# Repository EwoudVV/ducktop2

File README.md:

# Ducktop2

current case model, 10 october 2026. the lid and base share a 370 x 274 mm
outline, and the radio is planned as an external accessory. i'm aiming for
33.3 mm closed without feet. the right-side cooler and power guides now
clear the saved geometry, with no board cutout. the fan and fins now have
separate supports, with a bottom intake grille and a duct to the side.
the five selected feet bring the nominal total to 37.4 mm. the fan lead
extension has a route and removable clamp; the loaded intake gap and
finished wiring still need a physical check.
the cpu clamp and real material, load and cooling tests are still needed.
[case CAD and fit notes](mechanical/flush-case/README.md)

i'm building a 16-inch x86 laptop around the LattePanda Mu Ultra. i wanted the
exposed hardware and flexibility of a cyberdeck in something i could
actually carry around and use every day.

ducktop1 used a Pi 500+ and a portable monitor, with HDMI and USB-C cables
looping around the outside of the case. ducktop2 brings the display onto
direct eDP and puts power, ports, and laptop controls on custom boards.

## what's in it

- LattePanda Mu Ultra 226V initially, with the carrier designed to support a later 256V upgrade; 16 GB RAM and NVMe storage
- 16-inch AUO B160QAN03.K, targeting 2560x1600 at 120 Hz over direct eDP
- M.2 NVMe and a separate Wi-Fi/Bluetooth socket
- 65-key Cherry MX Ultra Low Profile keyboard and a 140 x 105 mm USB trackpad
- five USB-C ports, two USB-A ports, HDMI, and Gigabit Ethernet
- a 3S battery, USB-C PD charging from either side, and AUX/DC input
- STM32F407 for laptop control and a separate RP2350 with protected maker GPIO
- two status OLEDs, speakers, a headphone jack, and a microphone
- optional external VHF/UHF radio and GNSS accessory, with its own audio path

## build status

updated 16 october 2026. the carrier interface is being switched to Mu
Ultra: 226V first, with a later 256V upgrade. the new pin map moves HDMI to
TCP2, reallocates USB and gives NVMe a real clock-request connection. the
100 W power circuit is saved, but placement, routing, cooling and hardware
qualification still need work. the
[module requirements](manufacturing/lattepanda_mu_bios_release.md) separate
that target from the current CAD and the remaining hardware checks.

the revised power circuits, separate power wiring and signal connectors are
saved on all three main boards. the new placement pass uses both sides:
local capacitors sit near their actual supply pins, USB protection follows
its connector, and the audio and maker circuits have been regrouped.
the connector positions, mounting points and board gaps are preserved.
the existing PCIe routing is intact. the latest pass moves 31 power parts,
adds five local capacitors, repairs the right USB-C control routes and
corrects three USB protection footprints to their proper 0.4 mm pitch.
[placement and checks](docs/hardware/mainboard-power-placement.md) cover
those changes.

20 october: the charger and the Mu supply are routed, including both
controllers and a VSYS island on In4. their local parts were re-placed so the
fine-pitch controller pins could escape cleanly.
[charger and Mu supply routing](docs/hardware/charger-and-mu-routing.md)
has the details. the input selectors, battery path, fuel gauge and
always-on chain are routed locally as well; both selectors moved to the back
and the gauge shunt now sits beside the battery terminal.
[input and battery routing](docs/hardware/input-and-battery-routing.md)
covers that pass. DRC has no new findings and the unconnected count dropped
from 1,798 to 1,308. the long feeds from the side terminals and most of the
main-board routing still remain.

the keyboard has per-key RGB on four layers and its routing is complete.
the RGB buffer has separate 3.3 V and 5 V supplies. the key positions,
outline and cable connector are unchanged. [keyboard routing notes](keyboard/README.md)
cover the LEDs, current limit and switch keepouts. the old non-RGB order
files have been retired. the radio antenna connectors now match the board edge and their
mechanical drawing. the radio still needs routing.

the four-layer BMS is routed for stronger battery operation, with
an 8 A discharge target and up to 3 A charging. it now uses a BQ76922,
independent current guards and a limited startup branch. the 80 mm board
has zero unconnected items and zero physical DRC findings, including the
stricter fabrication checks. its first assembly leaves the three drive links
out for programming and bench tests. the matching center-board cutout is
saved. [power and battery](docs/hardware/power-and-battery.md) describes the
circuit and the measurements needed before using it with the cells.
the three main-board sections are eight layers,
and most of their routing still remains. [power revision status](docs/hardware/power-revision.md)
records what is saved and what is still unfinished.

firmware corrections cover charger communication, startup, watchdog and fan
handling, USB power permissions, and host communication. assembled-hardware
tests are still pending. the replacement panel has run at 2560x1600 and
120 Hz on the Intehill controller; the final Mu-to-panel cable still needs
validation. the complete laptop is not ready for fabrication or powered
integration.

## boards

```mermaid
flowchart LR
    L[Left I/O] <-->|signal cable and power wiring| C[Center: Mu, EC, charger, gauge, maker MCU]
    C <-->|signal cable and power wiring| R[Right I/O]
    B[BMS: cell monitoring and protection] <-->|power and isolated control wiring| C
    Cells[3S cells and cell taps] --- B
    C --- K[Keyboard]
    C --- Radio[Optional external radio and GNSS]
    C -->|Mu onboard eDP| Panel[Internal display]
```

the center charges the whole pack. the BMS monitors the cell taps and
controls the protection FETs. balancing is disabled in the prototype profile.
the EC and maker controller have separate jobs,
and the rest of the laptop is intended to work with the radio board removed.

## open in KiCad

the current reference version is KiCad 10.0.4.

| Work | File |
| --- | --- |
| Center schematic | `ducktop2.kicad_pro` |
| Center layout | `ducktop2-center.kicad_pcb` |
| Left I/O | `left_io/left_io.kicad_pro` |
| Right I/O | `right_io/right_io.kicad_pro` |
| BMS | `bms/bms.kicad_pro` |
| Keyboard | `keyboard/12_keyboard_daughterboard.kicad_pro` |
| Radio | `radio_daughterboard/radio_daughterboard.kicad_pro` |

read [build and verification](docs/build-and-verify.md) before regenerating
or syncing a board. the center schematic and PCB have different basenames.
review an explicit current netlist before updating the PCB; rebuilding a
board can replace existing routing.

## files and documentation

| Location | Contents |
| --- | --- |
| Root KiCad files | Center project and active schematic hierarchy |
| `left_io/`, `right_io/`, `bms/`, `keyboard/`, `radio_daughterboard/` | Separate board projects |
| `gen/` | Schematic generators, validation code, and symbol definitions |
| `ducktop2.pretty/`, `Module_LattePanda.pretty/`, `ducktop2.3dshapes/` | Shared footprints and models |
| `docs/hardware/` | Circuit, cable, display, and mechanical documentation |
| `firmware/` | EC/maker code, tests, and firmware release records |
| `mechanical/` | Floorplan, case CAD, layout planner and fit checks |
| `reference/` | Source/reference designs and retained generator inputs |
| `manufacturing/` | Board packages, quotes, and manufacturing requirements |
| `verification/` | Hardware validation record and ignored generated checks |
| `software/` | Fedora setup, recovery, and theme files |

- [hardware and behavior](docs/hardware/overview.md)
- [power and battery](docs/hardware/power-and-battery.md)
- [cables and connectors](docs/hardware/cables-and-connectors.md)
- [display harness](docs/hardware/display-direct-edp.md)
- [mechanical layout](docs/hardware/mechanical.md)
- [build and verify](docs/build-and-verify.md)
- [bring-up procedure](docs/BRINGUP_TEST_PLAN.md)
- [parts and cost](docs/bom-and-cost.md)
- [firmware](firmware/README.md)
- [manufacturing](manufacturing/README.md)
- [OS work](software/os-theme/README.md)
- [ducktop1](docs/ducktop1.md)
- [Forge project pitch](docs/forgery_pitch.md)
- [project journal](JOURNAL.md)

## sponsors

thanks to NextPCB for supporting PCB manufacturing and assembly for ducktop2!

## license

the project files are under the [MIT license](LICENSE).

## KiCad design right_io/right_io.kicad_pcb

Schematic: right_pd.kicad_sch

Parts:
C1760: 100n branch input; C_0603_1608Metric; MPN GRM188R71H104KA93D
C1761: 100n TPS25810 IN HF; C_0603_1608Metric; MPN GRM188R71H104KA93D
C1762: 150u 10V TPS25810 input reservoir; CP_EIA-7343-31_Kemet-D; MPN T520D157M010ATE025
C1763: 10u protected VBUS_SYS; C_1206_3216Metric; MPN GRM31CR71A106KA01L
C1764: 100n TPS25810 AUX; C_0603_1608Metric; MPN GRM188R71H104KA93D
C1770: 1u 50V connector-side VBUS; C_0805_2012Metric; MPN GRM21BR71H105KA12L
C1771: 1u TPD1S514 VBUS_POWER stability; C_0603_1608Metric; MPN GRM188R71A105KA61D
C2040: 100n 100V TPD4S201 VBIAS; C_0805_2012Metric; MPN GRM21BR72A104KA01L
C2041: 820n 10V TPD4S201 VPWR; C_0805_2012Metric; MPN GRM21BR71A824KA01L
C2042: 100n EEPROM local; C_0603_1608Metric; MPN GRM188R71H104KA93D
C2043: 100n mux-control buffer local; C_0603_1608Metric; MPN GRM188R71H104KA93D
C2055: 4.7u 25V raw VBUS; pre-attach total below 10uF; C_1206_3216Metric; MPN GRM31CR71E475KA88L
C2056, C2057, C2058, C2059: 10n 50V connector VBUS HF; C_0402_1005Metric; MPN GRM155R71H103KA88D
C2060: 10u 25V X7R; C_1206_3216Metric; MPN GRM31CR71E106KA12L
C2061, C2693: 4.7u 25V X7R; C_1206_3216Metric; MPN GRM31CR71E475KA88L
C2062: 10u 10V X7R; C_1206_3216Metric; MPN GRM31CR71A106KA01L
C2063, C2064: 270p C0G; C_0402_1005Metric; MPN GRM1555C1H271JA01D
C2065, C2066: 100u 10V PP5V source bulk; CP_EIA-7343-31_Kemet-D; MPN T520D107M010ATE070
C2067: 10u PP5V local ceramic; C_1206_3216Metric; MPN GRM31CR71A106KA01L
C2068: 68u 25V PPHV sink bulk; CP_EIA-7343-31_Kemet-D; MPN T521V686M025ATE050
C2069: 100n 50V PPHV local; C_0603_1608Metric; MPN GRM188R71H104KA93D
C2070: 100n USB2 switch local; C_0603_1608Metric; MPN GRM188R71H104KA93D
C2090: 100n 50V input local; C_0603_1608Metric; MPN GRM188R71H104KA93D
C2091: 10u 25V output; C_1206_3216Metric; MPN GRM31CR71E106KA12L
C2092: 10n 50V C0G slew control; C_0603_1608Metric; MPN GRM1885C1H103JA01D
C2404: 1u; C_0805_2012Metric; MPN GRM21BR71H105KA12L
C2409: 100n; C_0603_1608Metric; MPN GRM188R71H104KA93D
C2414: 4.7n C0G PP5V slew; C_0603_1608Metric; MPN GRM1885C1H472JA01D
C2631: 100n 50V inverter bypass; C_0603_1608Metric; MPN GRM188R71H104KA93D
C2681: 100n 50V qualifier bypass; C_0603_1608Metric; MPN GRM188R71H104KA93D
D2090: B340A eFuse output negative-transient clamp; D_SMA; MPN B340A-13-F
H13, H15, H17: M2.5 isolated mainboard mounting hole; MountingHole_2.7mm_M2.5
J11: USB-C dual-role data/PD port J11; USB_C_Receptacle_Molex_105450-0101; MPN 105450-0101
J12: USB-C source-only data port J12; USB_C_Receptacle_Molex_105450-0101; MPN 105450-0101
Q2002: 2N7002K DFP USB2 enable inverter; SOT-23; MPN 2N7002KT1G
Q2631: BSS138 switched discharge; SOT-23; MPN BSS138LT1G
R1760: 19.1k 1% TPS2553 VBUS plus VCONN ILIM; R_0603_1608Metric; MPN RC0603FR-0719K1L
R1761: 4.99k POL pull-up; R_0603_1608Metric; MPN RC0603FR-074K99L
R1762: 100k 1% TPS25810 REF; R_0603_1608Metric; MPN RC0603FR-07100KL
R1770: 249R 0.25W TPS25810 OUT discharge; R_1206_3216Metric; MPN RC1206FR-07249RL
R2040: 10k shared CC/USB2 protector FLT pull-up; R_0603_1608Metric; MPN RC0603FR-0710KL
R2041: 2.2k EEPROM SDA pull-up; R_0603_1608Metric; MPN RC0603FR-072K2L
R2042: 2.2k EEPROM SCL pull-up; R_0603_1608Metric; MPN RC0603FR-072K2L
R2043: 4.7k TCPC SDA pull-up; R_0603_1608Metric; MPN RC0603FR-074K7L
R2044: 4.7k TCPC SCL pull-up; R_0603_1608Metric; MPN RC0603FR-074K7L
R2045: 10k TCPC IRQ pull-up; R_0603_1608Metric; MPN RC0603FR-0710KL
R2046: 10k mux FLIP pull-up; R_0603_1608Metric; MPN RC0603FR-0710KL
R2047: 10k mux EN pull-up; R_0603_1608Metric; MPN RC0603FR-0710KL
R2055: 10k I2Cc IRQ inactive pull-up; R_0603_1608Metric; MPN RC0603FR-0710KL
R2056: 100k USB2 switch default-disable pull-up; R_0603_1608Metric; MPN RC0603FR-07100KL
R2057: 0R protector FLT wired-OR link; R_0603_1608Metric; MPN RC0603FR-070RL
R2090: 1k 1W switched input discharge; R_2512_6332Metric; MPN RC2512FR-071KL
R2091: 100k discharge gate default-low; R_0603_1608Metric; MPN RC0603FR-07100KL
R2092: 1k IMON load; R_0603_1608Metric; MPN RC0603FR-071KL
R2093: 267R 0.1% sink breaker; 5.58A nominal; R_0603_1608Metric; MPN RT0603BRD07267RL
R2094: 47k sink enable default-off; R_0603_1608Metric; MPN RC0603FR-0747KL
R2095: 10k sink enable series; R_0603_1608Metric; MPN RC0603FR-0710KL
R2096: 150k sink PG pull-up; valid with input off; R_0603_1608Metric; MPN RC0603FR-07150KL
R2404, R2409: 100k; R_0603_1608Metric; MPN RC0603FR-07100KL
R2414: 10k; R_0603_1608Metric; MPN RC0603FR-0710KL
U42: TPS25751AD USB-PD DRP controller; Texas_REF0038A_WQFN-38-2EP_6x4mm_P0.4; MPN TPS25751ADREFR
U721: TPS259827ONRGER PD2 sink breaker; Texas_RGE0024M_QFN24_4x4_2EP; MPN TPS259827ONRGER
U1760: TPS2553DDBVR 1.3A USB branch; SOT-23-6; MPN TPS2553DDBVR
U1761: TPS25810RVCR Type-C DFP controller; Texas_RVC0020A_WQFN-20-1EP_3x4mm_P0.5mm_EP1.6x2.6mm; MPN TPS25810RVCR
U1763: TPD1S514-1YZR 5.9V VBUS OVP; Texas_TPD1S514_YZ0012_1.99x1.29mm_P0.4mm; MPN TPD1S514-1YZR
U1765: TPD4E05U06 USB2/CC ESD; USON-10_2.5x1.0mm_P0.5mm; MPN TPD4E05U06DQAR
U2011: TPD4S201 CC and USB2 short-to-VBUS protector; Texas_RUK0020B_WQFN-20-1EP_3x3mm_P0.4mm_EP1.7x1.7mm_Thermal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; MPN TPD4S201RUKR
U2012: CAT24C256 32KB private TPS25751A EEPROM; SOIC-8_3.9x4.9mm_P1.27mm; MPN CAT24C256WI-GT3
U2013: TS3USB30E DFP-qualified USB2 disconnect; TSSOP-10_3x3mm_P0.5mm; MPN TS3USB30EDGSR
U2014: SN74LVC2G07 partial-power-down mux controls; SOT-363_SC-70-6; MPN SN74LVC2G07DCKR
U2015: TVS2200 22V USB VBUS surge clamp; WSON-6-1EP_2x2mm_P0.65mm_EP1x1.6mm; MPN TVS2200DRVR
U2016: SN74LVC1G08 DFP and attached qualifier; SOT-23-5; MPN SN74LVC1G08DBVR
U2404: TPS22992SRXNR J11 PP5V gate; Texas_RXN0008A_WQFN-HR-8_1.25x1.25mm; MPN TPS22992SRXNR
U2409: SN74LVC1G08DBVR J12 source permission; SOT-23-5; MPN SN74LVC1G08DBVR
U2631: SN74LVC1G04DBVR discharge control; SOT-23-5; MPN SN74LVC1G04DBVR

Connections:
/HUB_DS1_DN: U2013.8 (D1-); also elsewhere on the board
/HUB_DS1_DP: U2013.2 (D1+); also elsewhere on the board
/HUB_DS4_DN: J12.A7 (D-), J12.B7 (D-), U1765.2 (D1-); also elsewhere on the board
/HUB_DS4_DP: J12.A6 (D+), J12.B6 (D+), U1765.1 (D1+); also elsewhere on the board
/HUB_PRT_CTL4: U1760.4 (~FAULT), U1761.1 (~FAULT), U2409.2; also elsewhere on the board
/MCU_3V3: C2062.1, C2409.1, C2631.1, R2040.1, R2043.1, R2044.1, R2045.1, R2096.1, U42.38 (VIN_3V3), U2409.5 (VCC), U2631.5 (VCC); also elsewhere on the board
/PD2 Dual-Role/J11_PP5V_CT: C2414.1, U2404.7 (CT)
/PD2 Dual-Role/J12_5V_PRE: C1761.1, C1762.1, U1760.6 (OUT), U1761.2 (IN1), U1761.3 (IN1), U1761.4 (IN2)
/PD2 Dual-Role/J12_CC1: J12.A5 (CC1), U1761.11 (CC1), U1765.4 (D2+)
/PD2 Dual-Role/J12_CC2: J12.B5 (CC2), U1761.13 (CC2), U1765.5 (D2-)
/PD2 Dual-Role/J12_ILIM: R1760.1, U1760.5 (ILIM)
/PD2 Dual-Role/J12_POL_N: R1761.2, U1761.18 (~POL)
/PD2 Dual-Role/J12_REF: R1762.1, U1761.10 (REF)
/PD2 Dual-Role/J12_REF_RTN: R1762.2, U1761.9 (REF_RTN)
/PD2 Dual-Role/J12_VBUS: C1770.1, J12.A4 (VBUS), J12.A9 (VBUS), J12.B4 (VBUS), J12.B9 (VBUS), U1763.B3 (VBUS_CON), U1763.C2 (VBUS_CON), U1763.C3 (VBUS_CON)
/PD2 Dual-Role/J12_VBUS_POWER: C1771.1, U1763.B1 (VBUS_POWER)
/PD2 Dual-Role/J12_VBUS_SYS: C1763.1, R1770.1, U1761.14 (OUT), U1761.15 (OUT), U1763.A2 (VBUS_SYS), U1763.A3 (VBUS_SYS), U1763.B2 (VBUS_SYS)
/PD2 Dual-Role/PD2_CC1_CONN: J11.A5 (CC1), U2011.4 (C_CC1), U2011.7 (RPD_G1)
/PD2 Dual-Role/PD2_CC1_SYS: C2063.1, U42.28 (CC1), U2011.12 (CC1)
/PD2 Dual-Role/PD2_CC2_CONN: J11.B5 (CC2), U2011.5 (C_CC2), U2011.6 (RPD_G2)
/PD2 Dual-Role/PD2_CC2_SYS: C2064.1, U42.29 (CC2), U2011.11 (CC2)
/PD2 Dual-Role/PD2_CC_ESD_VBIAS: C2040.1, U2011.3 (VBIAS)
/PD2 Dual-Role/PD2_CC_FAULT_LOCAL_N: R2057.1, U2011.9 (FLT)
/PD2 Dual-Role/PD2_CONN_DN: J11.A7 (D-), J11.B7 (D-), U2011.2 (C_SBU2)
/PD2 Dual-Role/PD2_CONN_DP: J11.A6 (D+), J11.B6 (D+), U2011.1 (C_SBU1)
/PD2 Dual-Role/PD2_DISCHARGE: Q2631.1 (G), R2091.1, U2631.4
/PD2 Dual-Role/PD2_DISCHARGE_DRAIN: Q2631.3 (D), R2090.2
/PD2 Dual-Role/PD2_DRAIN_THERMAL: U42.15 (DRAIN), U42.30 (DRAIN), U42.40 (DRAIN)
/PD2 Dual-Role/PD2_EEPROM_IRQ_N: R2055.2, U42.18 (I2Cc_IRQ)
/PD2 Dual-Role/PD2_EEPROM_SCL: R2042.2, U42.17 (I2Cc_SCL), U2012.6 (SCL)
/PD2 Dual-Role/PD2_EEPROM_SDA: R2041.2, U42.16 (I2Cc_SDA), U2012.5 (SDA)
/PD2 Dual-Role/PD2_EFUSE_DVDT: C2092.1, U721.15 (dVdt)
/PD2 Dual-Role/PD2_EFUSE_ILIM: R2093.1, U721.8 (ILIM)
/PD2 Dual-Role/PD2_EFUSE_IMON: R2092.1, U721.9 (IMON)
/PD2 Dual-Role/PD2_EFUSE_SHDN: R2094.1, R2095.2, U721.6 (EN/UVLO)
/PD2 Dual-Role/PD2_GPIO_ATTACH: U42.36 (GPIO7), U2016.2
/PD2 Dual-Role/PD2_GPIO_DFP: U42.26 (GPIO4/USB_P), U2016.1
/PD2 Dual-Role/PD2_GPIO_FLIP: U42.37 (GPIO6), U2014.1
/PD2 Dual-Role/PD2_HOST_ATTACHED: U2014.3, U2016.4
/PD2 Dual-Role/PD2_HOST_SWITCHED_DN: U2011.14 (SBU2), U2013.6 (D-)
/PD2 Dual-Role/PD2_HOST_SWITCHED_DP: U2011.15 (SBU1), U2013.4 (D+)
/PD2 Dual-Role/PD2_LDO1V5: C2061.1, C2693.1, U42.4 (LDO_1V5)
/PD2 Dual-Role/PD2_LDO3V3: C2041.1, C2042.1, C2060.1, R2041.1, R2042.1, R2055.1, U42.1 (LDO_3V3), U2011.10 (VPWR), U2012.8 (VCC)
/PD2 Dual-Role/PD2_MUX_EN: Q2002.1 (G), R2047.2, U2014.4
/PD2 Dual-Role/PD2_MUX_FLIP: R2046.2, U2014.6
/PD2 Dual-Role/PD2_PP5V_GATED: C2065.1, C2066.1, C2067.1, R2414.1, U42.34 (PP5V_(34-35)), U2404.5 (QOD), U2404.6 (VOUT)
/PD2 Dual-Role/PD2_PPHV: C2068.1, C2069.1, C2090.1, U42.20 (PPHV_(20-22)), U721.1 (IN), U721.2 (IN), U721.3 (IN), U721.16 (IN), U721.25 (IN)
/PD2 Dual-Role/PD2_USB2_OE_N: Q2002.3 (D), R2056.2, U2013.9 (~OE)
/PD2 Dual-Role/USB_J12_SWITCH_EN: U1760.3 (EN), U1761.6 (EN), U2409.4
/PD2_EFUSE_PG: R2096.2, U721.13 (PG); also elsewhere on the board
/PD2_I2C_SCL: R2044.2, U42.9 (I2Ct_SCL); also elsewhere on the board
/PD2_I2C_SDA: R2043.2, U42.8 (I2Ct_SDA); also elsewhere on the board
/PD2_PATH_EN: R2095.1, U2631.2; also elsewhere on the board
/PD2_SOURCE_PG: R2414.2, U2404.3 (PG); also elsewhere on the board
/PD2_TCPC_IRQ_N: R2045.2, U42.10 (I2Ct_IRQ); also elsewhere on the board
/PD2_VBUS_GATED: C2091.1, D2090.1 (K), R2090.1, U721.17 (OUT), U721.18 (OUT), U721.19 (OUT), U721.20 (OUT), U721.21 (OUT), U721.22 (OUT), U721.23 (OUT), U721.24 (OUT); also elsewhere on the board
/PD2_VBUS_RAW: C2055.1, C2056.1, C2057.1, C2058.1, C2059.1, J11.A4 (VBUS), J11.A9 (VBUS), J11.B4 (VBUS), J11.B9 (VBUS), U42.23 (VBUS_IN_(23-25)), U42.32 (VBUS_(32-33)), U2015.4 (IN), U2015.5 (IN), U2015.6 (IN); also elsewhere on the board
/PD_PROTECT_FAULT_N: R2040.2, R2057.2; also elsewhere on the board
/SYS_3V3: C1764.1, C2043.1, C2070.1, C2681.1, R1761.1, R2046.1, R2047.1, R2056.1, U1761.5 (AUX), U2013.10 (VCC), U2014.5 (VCC), U2016.5 (VCC); also elsewhere on the board
/USB_J11_PERMIT: R2404.1, U2404.8 (ON); also elsewhere on the board
/USB_J12_PERMIT: R2409.1, U2409.1; also elsewhere on the board
/USB_PORT_5V: C1760.1, C2404.1, U1760.1 (IN), U2404.1 (VBIAS), U2404.2 (VIN); also elsewhere on the board
GND: C1760.2, C1761.2, C1762.2, C1763.2, C1764.2, C1770.2, C1771.2, C2040.2, C2041.2, C2042.2, C2043.2, C2055.2, C2056.2, C2057.2, C2058.2, C2059.2, C2060.2, C2061.2, C2062.2, C2063.2, C2064.2, C2065.2, C2066.2, C2067.2, C2068.2, C2069.2, C2070.2, C2090.2, C2091.2, C2092.2, C2404.2, C2409.2, C2414.2, C2631.2, C2681.2, C2693.2, D2090.2 (A), J11.A1 (GND), J11.A12 (GND), J11.B1 (GND), J11.B12 (GND), J11.SH (SHIELD), J12.A1 (GND), J12.A12 (GND), J12.B1 (GND), J12.B12 (GND), J12.SH (SHIELD), Q2002.2 (S), Q2631.2 (S), R1760.2, R1770.2, R2091.2, R2092.2, R2093.2, R2094.2, R2404.2, R2409.2, U42.2 (ADCIN1), U42.3 (ADCIN2), U42.5 (GPIO0/LD1), U42.6 (GPIO1), U42.7 (GPIO2/LD2), U42.11 (GND), U42.12 (GND), U42.13 (GPIO11), U42.14 (GND), U42.19 (GPIO3), U42.27 (GPIO5/USB_N), U42.31 (GND), U42.39 (GND), U721.4 (GND), U721.5 (GND), U721.10 (RETRY_DLY), U721.11 (NRETRY), U721.12 (LDSTRT), U721.14 (GND), U721.26 (GND), U1760.2 (GND), U1761.7 (CHG), U1761.8 (CHG_HI), U1761.12 (GND), U1761.21 (GND), U1763.A1 (EN_N), U1763.A4 (GND), U1763.B4 (GND), U1763.C1 (GND), U1763.C4 (GND), U1765.3 (GND), U1765.8 (GND), U2011.8 (GND), U2011.13 (GND), U2011.18 (GND), U2011.21 (GND), U2012.1 (A0), U2012.2 (A1), U2012.3 (A2), U2012.4 (GND), U2012.7 (WP), U2013.1 (S), U2013.5 (GND), U2014.2 (GND), U2015.1 (GND), U2015.2 (GND), U2015.3 (GND), U2015.7 (GND), U2016.3 (GND), U2404.4 (GND), U2409.3 (GND), U2631.3 (GND); also elsewhere on the board

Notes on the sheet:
== Right I/O: PD2 dual-role (J11) + source (J12), USB2-only ==
== J11: USB 2.0 data plus USB-PD charging, side port 2 ==
J11: hardware accepts 15V/20V PD; use a verified 3A contract and 2.50A IINDPM bootstrap command. Actual current/headroom and EEPROM/profile qualification remain required.
GPIO4 AND GPIO7 qualifies both host USB2 and SuperSpeed. They remain disconnected through reset, detach, and sink-only operation.
== J12: source-only USB-C data port, USB7206C downstream 4, USB2 ==

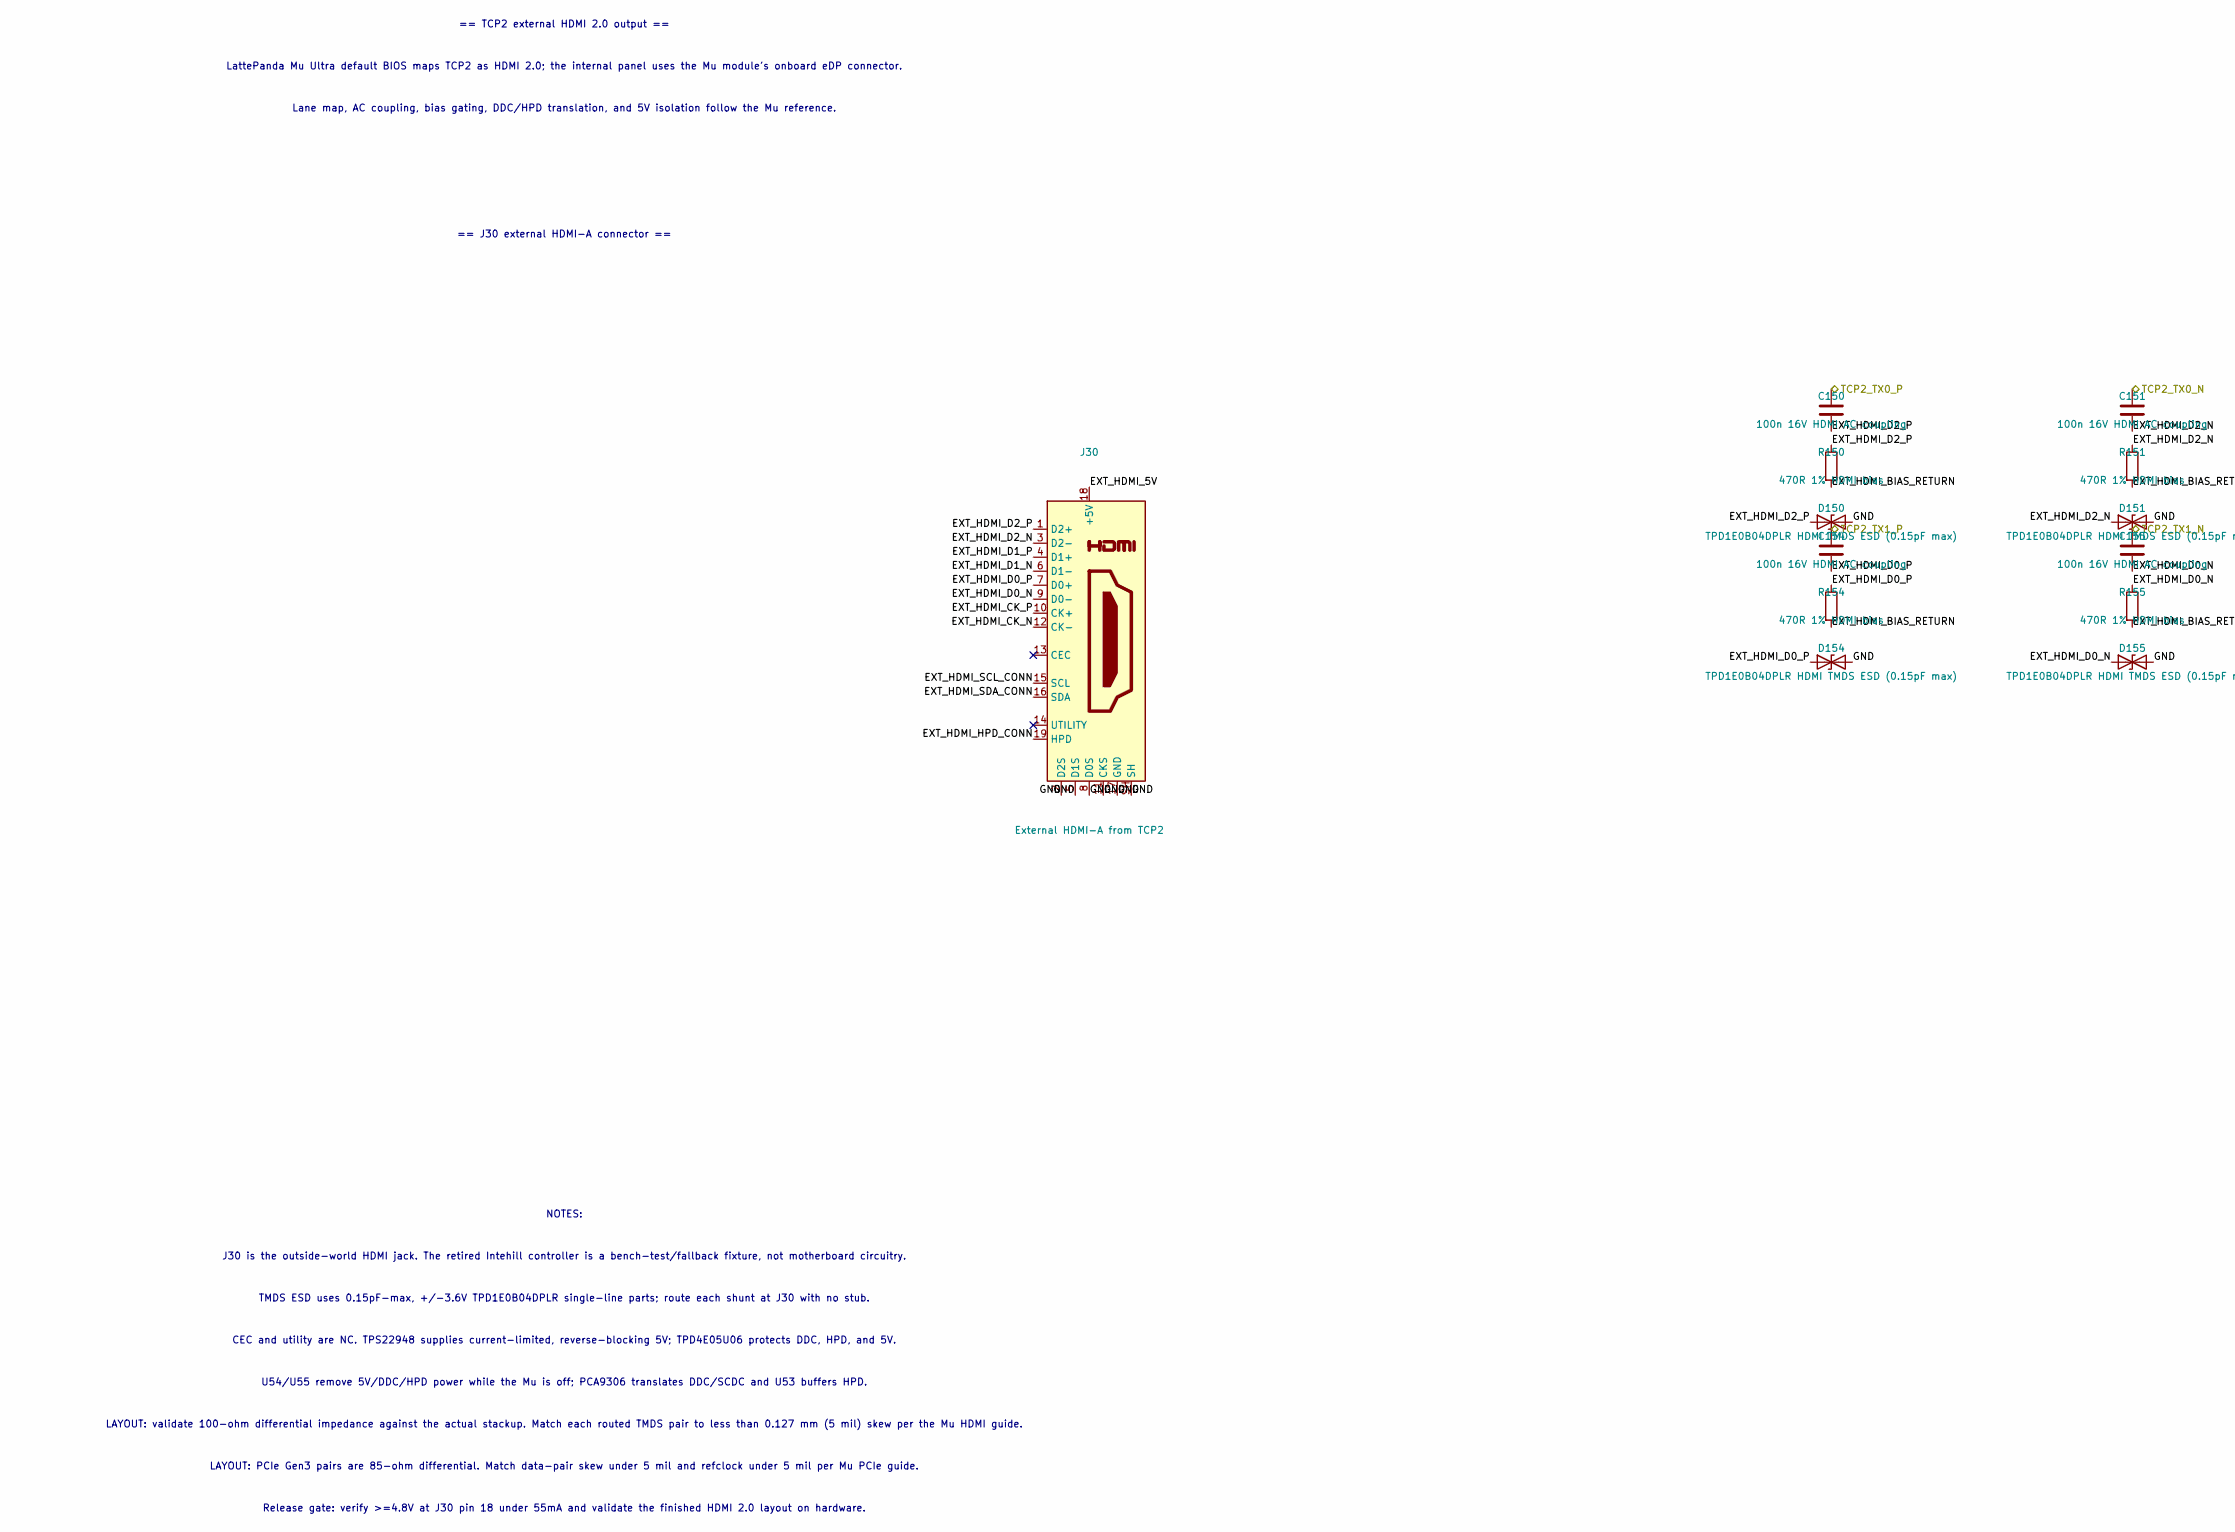
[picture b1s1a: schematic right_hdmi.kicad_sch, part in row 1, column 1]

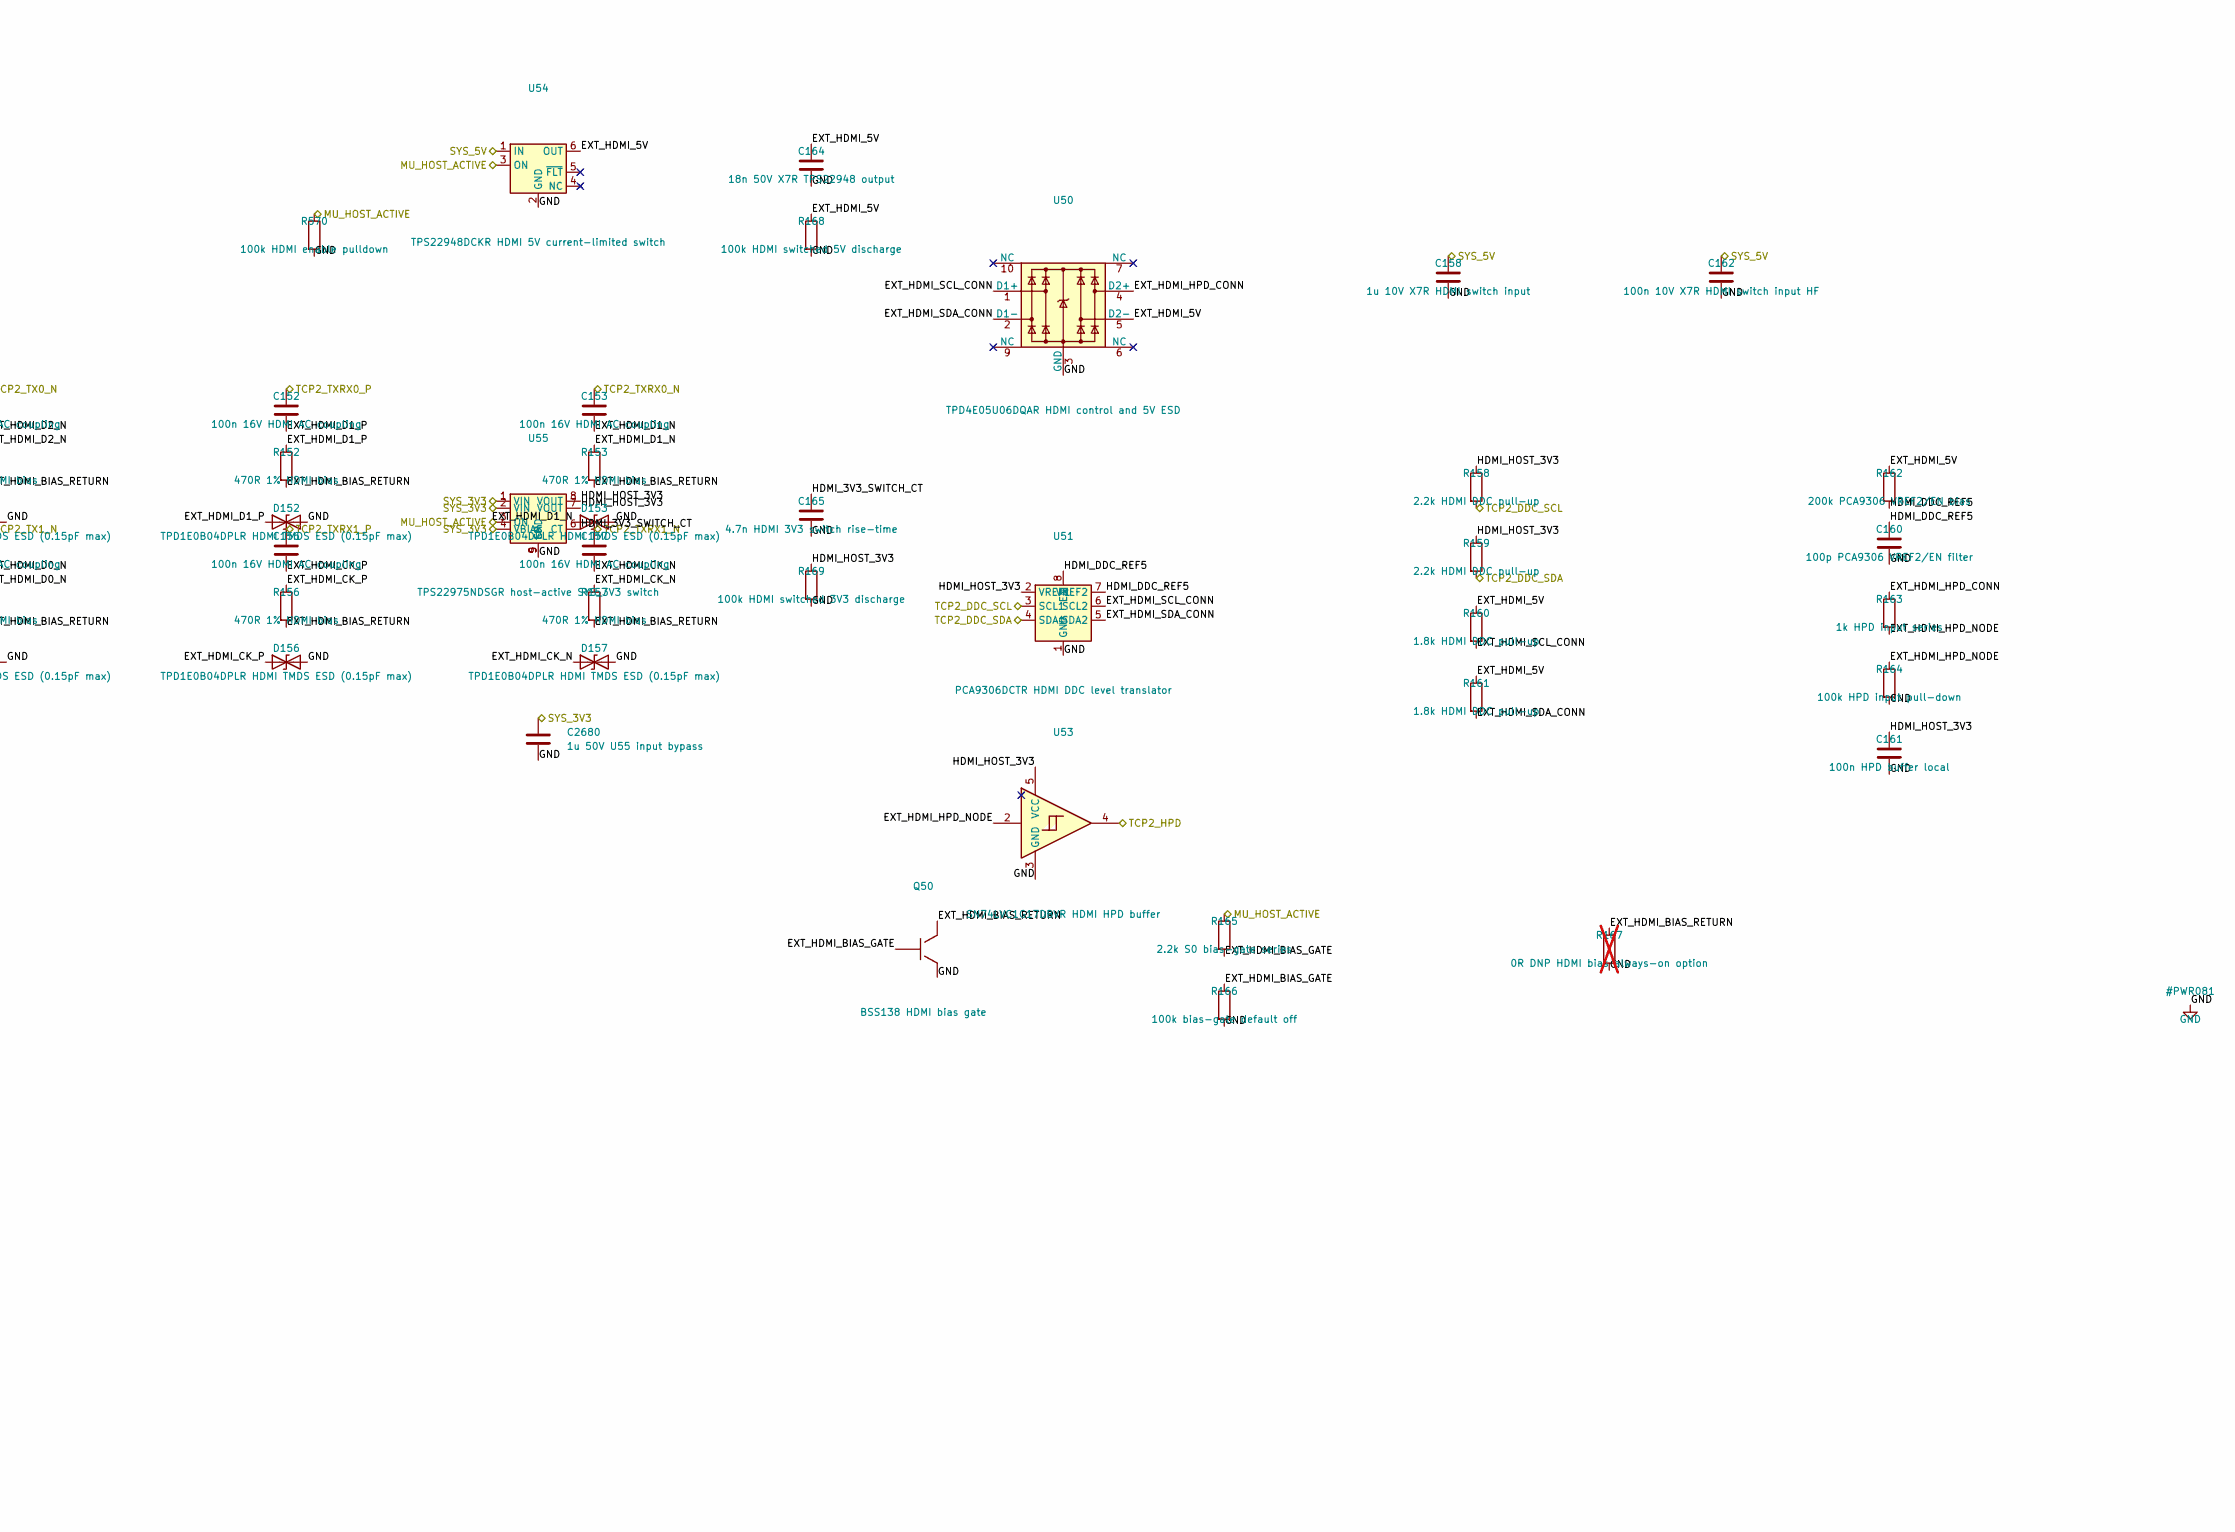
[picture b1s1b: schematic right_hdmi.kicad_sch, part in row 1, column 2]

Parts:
C150, C151, C152, C153, C154, C155, C156, C157: 100n 16V HDMI AC coupling; C_0402_1005Metric; MPN GRM155R71C104KA88D
C158: 1u 10V X7R HDMI switch input; C_0603_1608Metric; MPN GRM188R71A105KA61D
C160: 100p PCA9306 VREF2/EN filter; C_0402_1005Metric; MPN GRM1555C1H101JA01D
C161: 100n HPD buffer local; C_0402_1005Metric; MPN GRM155R71A104KA01D
C162: 100n 10V X7R HDMI switch input HF; C_0402_1005Metric; MPN GRM155R71A104KA01D
C164: 18n 50V X7R TPS22948 output; C_0402_1005Metric; MPN CC0402KRX7R9BB183
C165: 4.7n HDMI 3V3 switch rise-time; C_0402_1005Metric; MPN GRM155R71C472KA01D
C2680: 1u 50V U55 input bypass; C_0603_1608Metric; MPN GRT188R61H105ME13D
D150, D151, D152, D153, D154, D155, D156, D157: TPD1E0B04DPLR HDMI TMDS ESD (0.15pF max); D_0201_0603Metric; MPN TPD1E0B04DPLR
J30: External HDMI-A from TCP2; HDMI_A_Molex_208658-1001_Horizontal; MPN 208658-1001
Q50: BSS138 HDMI bias gate; SOT-23; MPN BSS138LT1G
R150, R151, R152, R153, R154, R155, R156, R157: 470R 1% HDMI bias; R_0402_1005Metric; MPN RC0402FR-07470RL
R158, R159: 2.2k HDMI DDC pull-up; R_0402_1005Metric; MPN RC0402FR-072K2L
R160, R161: 1.8k HDMI DDC pull-up; R_0402_1005Metric; MPN RC0402FR-071K8L
R162: 200k PCA9306 VREF2/EN bias; R_0402_1005Metric; MPN RC0402FR-07200KL
R163: 1k HPD input series; R_0402_1005Metric; MPN RC0402FR-071KL
R164: 100k HPD input pull-down; R_0402_1005Metric; MPN RC0402FR-07100KL
R165: 2.2k S0 bias-gate series; R_0402_1005Metric; MPN RC0402FR-072K2L
R166: 100k bias-gate default off; R_0402_1005Metric; MPN RC0402FR-07100KL
R167: 0R DNP HDMI bias always-on option; R_0402_1005Metric; not fitted
R168: 100k HDMI switched 5V discharge; R_0402_1005Metric; MPN RC0402FR-07100KL
R169: 100k HDMI switched 3V3 discharge; R_0402_1005Metric; MPN RC0402FR-07100KL
R570: 100k HDMI enable pulldown; R_0402_1005Metric; MPN RC0402FR-07100KL
U50: TPD4E05U06DQAR HDMI control and 5V ESD; USON-10_2.5x1.0mm_P0.5mm; MPN TPD4E05U06DQAR
U51: PCA9306DCTR HDMI DDC level translator; SSOP-8_2.95x2.8mm_P0.65mm; MPN PCA9306DCTR
U53: SN74LVC1G17DBVR HDMI HPD buffer; SOT-23-5; MPN SN74LVC1G17DBVR
U54: TPS22948DCKR HDMI 5V current-limited switch; SOT-363_SC-70-6; MPN TPS22948DCKR
U55: TPS22975NDSGR host-active SYS_3V3 switch; Texas_DSG0008A_WSON-8-1EP_2x2mm_P0.5mm_EP0.9x1.6mm; MPN TPS22975NDSGR

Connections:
/HDMI/EXT_HDMI_5V: C164.1, J30.18 (+5V), R160.1, R161.1, R162.1, R168.1, U50.5 (D2-), U54.6 (OUT)
/HDMI/EXT_HDMI_BIAS_GATE: Q50.1 (G), R165.2, R166.1
/HDMI/EXT_HDMI_BIAS_RETURN: Q50.3 (D), R150.2, R151.2, R152.2, R153.2, R154.2, R155.2, R156.2, R157.2, R167.1
/HDMI/EXT_HDMI_CK_N: C157.2, D157.1 (A1), J30.12 (CK-), R157.1
/HDMI/EXT_HDMI_CK_P: C156.2, D156.1 (A1), J30.10 (CK+), R156.1
/HDMI/EXT_HDMI_D0_N: C155.2, D155.1 (A1), J30.9 (D0-), R155.1
/HDMI/EXT_HDMI_D0_P: C154.2, D154.1 (A1), J30.7 (D0+), R154.1
/HDMI/EXT_HDMI_D1_N: C153.2, D153.1 (A1), J30.6 (D1-), R153.1
/HDMI/EXT_HDMI_D1_P: C152.2, D152.1 (A1), J30.4 (D1+), R152.1
/HDMI/EXT_HDMI_D2_N: C151.2, D151.1 (A1), J30.3 (D2-), R151.1
/HDMI/EXT_HDMI_D2_P: C150.2, D150.1 (A1), J30.1 (D2+), R150.1
/HDMI/EXT_HDMI_HPD_CONN: J30.19 (HPD), R163.1, U50.4 (D2+)
/HDMI/EXT_HDMI_HPD_NODE: R163.2, R164.1, U53.2
/HDMI/EXT_HDMI_SCL_CONN: J30.15 (SCL), R160.2, U50.1 (D1+), U51.6 (SCL2)
/HDMI/EXT_HDMI_SDA_CONN: J30.16 (SDA), R161.2, U50.2 (D1-), U51.5 (SDA2)
/HDMI/HDMI_3V3_SWITCH_CT: C165.1, U55.6 (CT)
/HDMI/HDMI_DDC_REF5: C160.1, R162.2, U51.7 (VREF2), U51.8 (EN)
/HDMI/HDMI_HOST_3V3: C161.1, R158.1, R159.1, R169.1, U51.2 (VREF1), U53.5 (VCC), U55.7 (VOUT), U55.8 (VOUT)
/MU_HOST_ACTIVE: R165.1, R570.1, U54.3 (ON), U55.3 (ON); also elsewhere on the board
/SYS_3V3: C2680.1, U55.1 (VIN), U55.2 (VIN), U55.4 (VBIAS); also elsewhere on the board
/SYS_5V: C158.1, C162.1, U54.1 (IN); also elsewhere on the board
/TCP2_DDC_SCL: R158.2, U51.3 (SCL1); also elsewhere on the board
/TCP2_DDC_SDA: R159.2, U51.4 (SDA1); also elsewhere on the board
/TCP2_HPD: U53.4; also elsewhere on the board
/TCP2_TX0_N: C151.1; also elsewhere on the board
/TCP2_TX0_P: C150.1; also elsewhere on the board
/TCP2_TX1_N: C155.1; also elsewhere on the board
/TCP2_TX1_P: C154.1; also elsewhere on the board
/TCP2_TXRX0_N: C153.1; also elsewhere on the board
/TCP2_TXRX0_P: C152.1; also elsewhere on the board
/TCP2_TXRX1_N: C157.1; also elsewhere on the board
/TCP2_TXRX1_P: C156.1; also elsewhere on the board
GND: C158.2, C160.2, C161.2, C162.2, C164.2, C165.2, C2680.2, D150.2 (A2), D151.2 (A2), D152.2 (A2), D153.2 (A2), D154.2 (A2), D155.2 (A2), D156.2 (A2), D157.2 (A2), J30.2 (D2S), J30.5 (D1S), J30.8 (D0S), J30.11 (CKS), J30.17 (GND), J30.SH, Q50.2 (S), R164.2, R166.2, R167.2, R168.2, R169.2, R570.2, U50.3 (GND), U50.8 (GND), U51.1 (GND), U53.3 (GND), U54.2 (GND), U55.5 (GND), U55.9 (EP); also elsewhere on the board

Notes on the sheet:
== TCP2 external HDMI 2.0 output ==
LattePanda Mu Ultra default BIOS maps TCP2 as HDMI 2.0; the internal panel uses the Mu module's onboard eDP connector.
Lane map, AC coupling, bias gating, DDC/HPD translation, and 5V isolation follow the Mu reference.
== J30 external HDMI-A connector ==
NOTES:
J30 is the outside-world HDMI jack. The retired Intehill controller is a bench-test/fallback fixture, not motherboard circuitry.
TMDS ESD uses 0.15pF-max, +/-3.6V TPD1E0B04DPLR single-line parts; route each shunt at J30 with no stub.
CEC and utility are NC. TPS22948 supplies current-limited, reverse-blocking 5V; TPD4E05U06 protects DDC, HPD, and 5V.
U54/U55 remove 5V/DDC/HPD power while the Mu is off; PCA9306 translates DDC/SCDC and U53 buffers HPD.
LAYOUT: validate 100-ohm differential impedance against the actual stackup. Match each routed TMDS pair to less than 0.127 mm (5 mil) skew per the Mu HDMI guide.
LAYOUT: PCIe Gen3 pairs are 85-ohm differential. Match data-pair skew under 5 mil and refclock under 5 mil per Mu PCIe guide.
Release gate: verify >=4.8V at J30 pin 18 under 55mA and validate the finished HDMI 2.0 layout on hardware.
